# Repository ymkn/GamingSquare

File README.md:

# GamingSquare

A customizable left-hand mechanical keyboard for gaming.

## LICENSE

This project is licensed under the MIT License, see the [LICENSE file](LICENSE) for details.

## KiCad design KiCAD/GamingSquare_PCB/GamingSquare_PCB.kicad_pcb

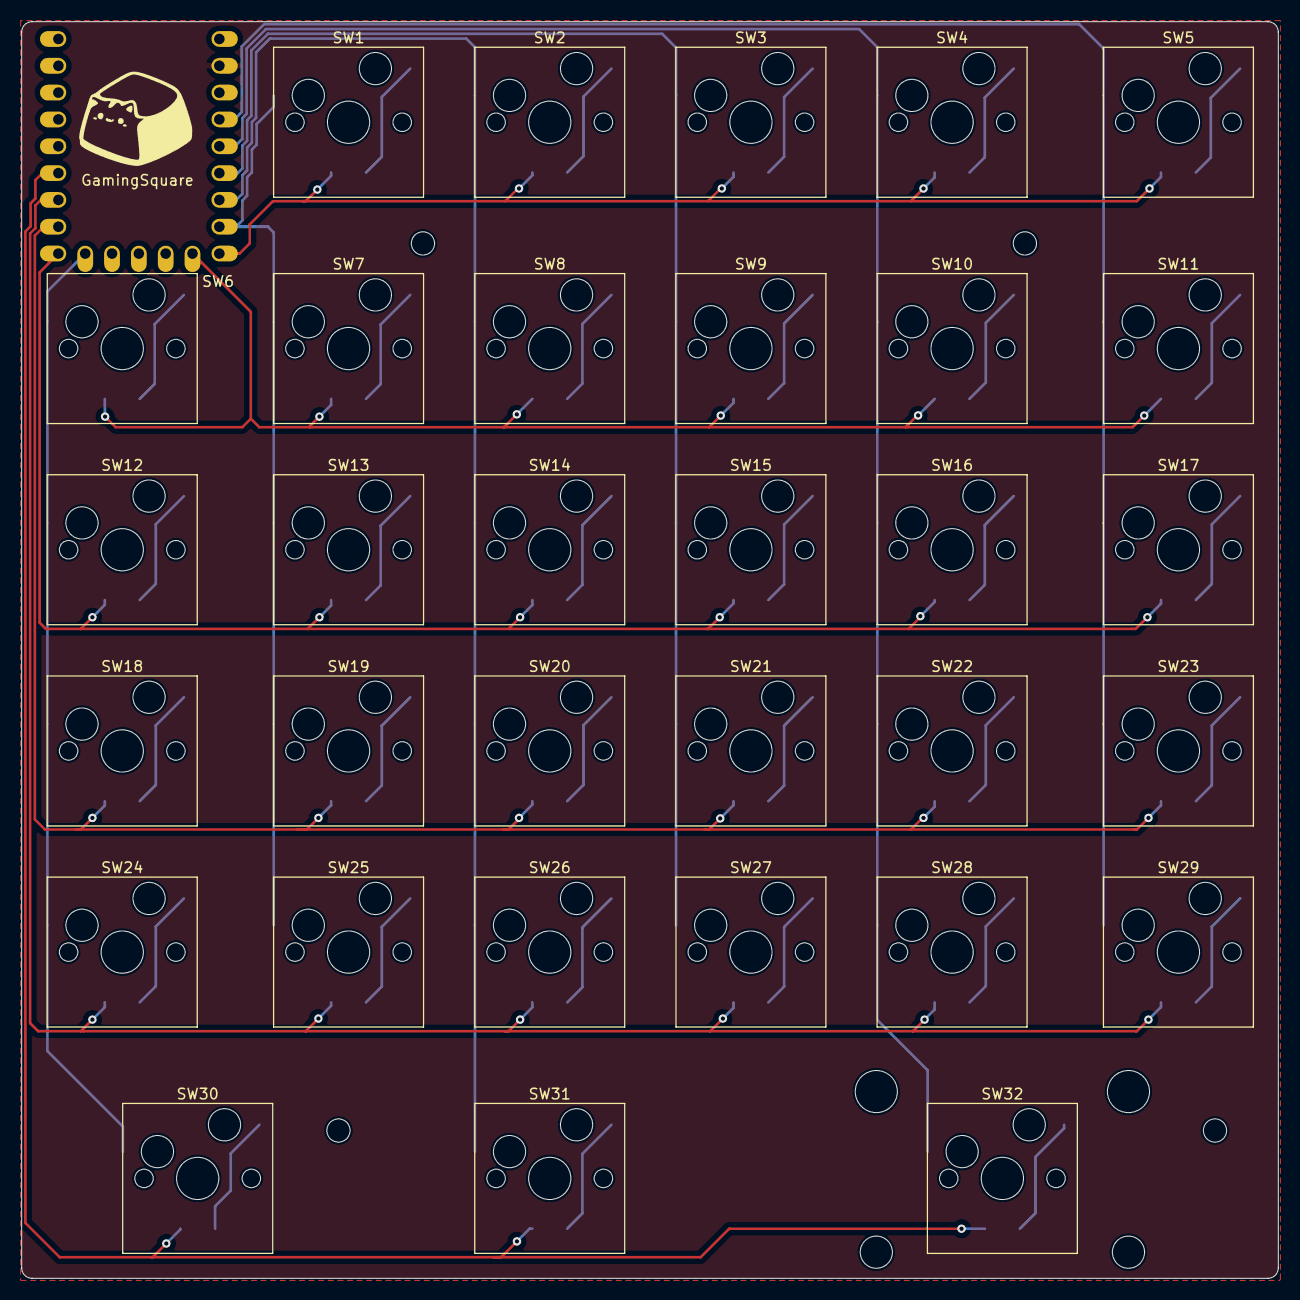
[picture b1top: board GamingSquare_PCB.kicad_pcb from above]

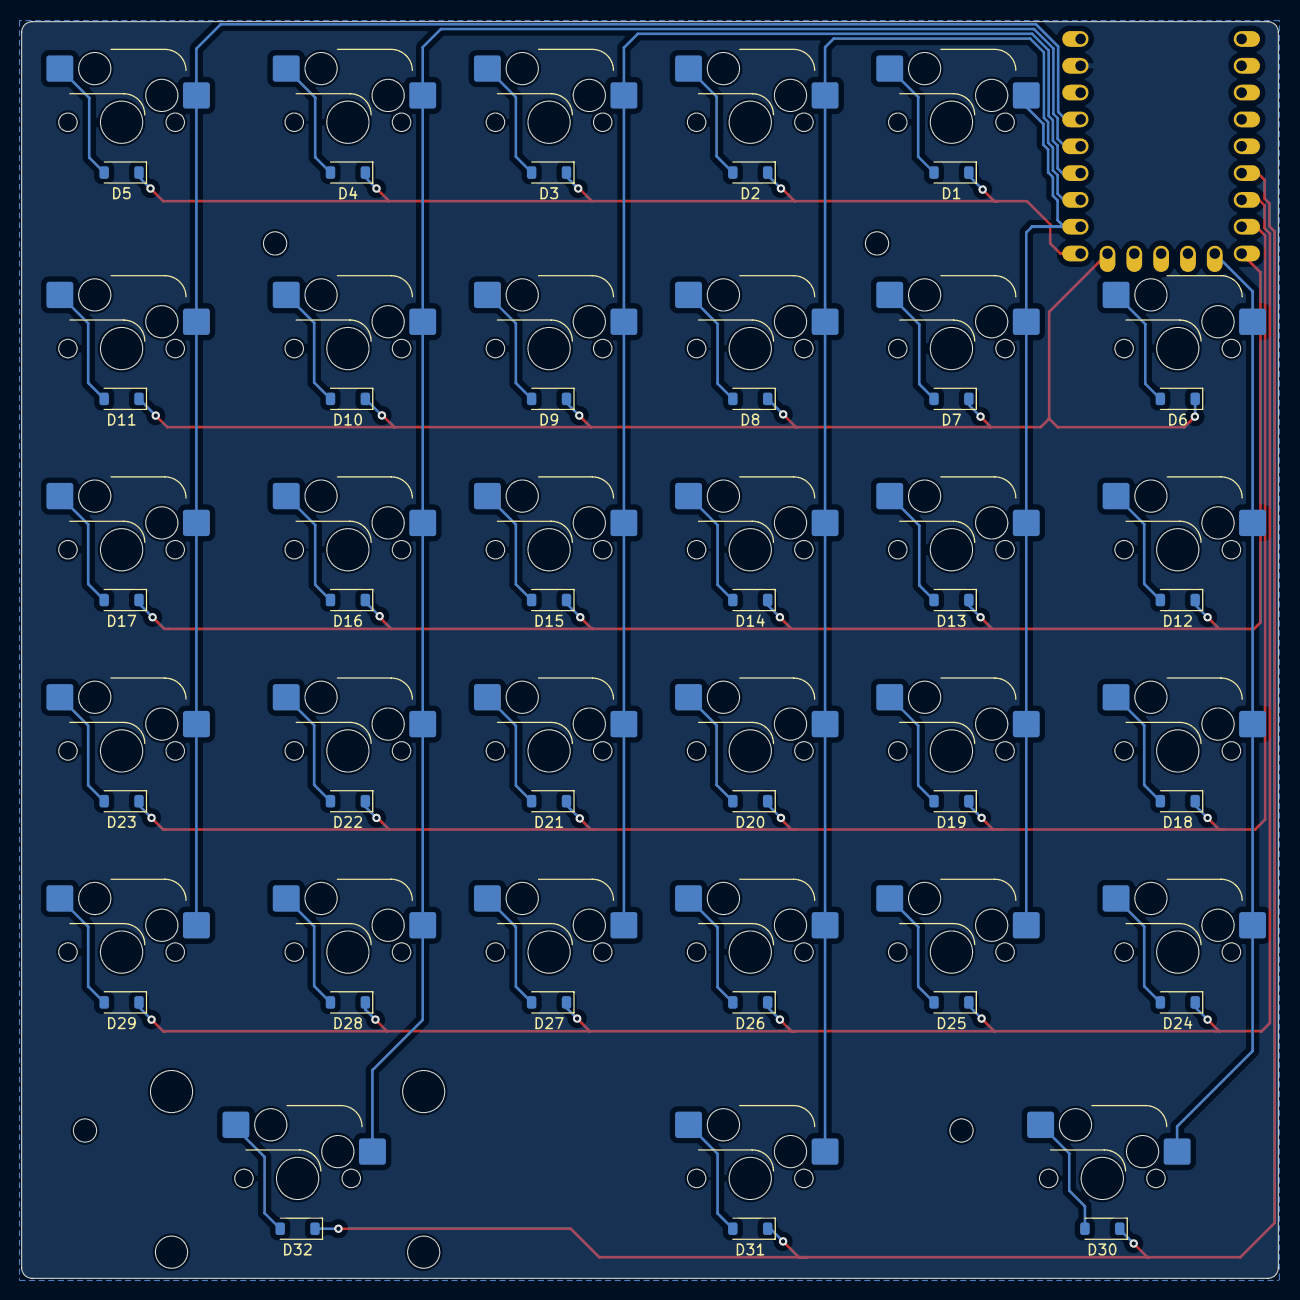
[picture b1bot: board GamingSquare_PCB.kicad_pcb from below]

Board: 2 copper layers, 119.0 x 119.0 mm, 65 parts (33 on the bottom side), 44 nets.

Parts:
D1, D2, D3, D4, D5, D6, D7, D8, D9, D10, D11, D12, D13, D14, D15, D16, D17, D18, D19, D20, D21, D22, D23, D24, D25, D26, D27, D28, D29, D30, D31, D32: 1N4148W; D_SOD-123
SW1, SW2, SW3, SW4, SW5, SW6, SW7, SW8, SW9, SW10, SW11, SW12, SW13, SW14, SW15, SW16, SW17, SW18, SW19, SW20, SW21, SW22, SW23, SW24, SW25, SW26, SW27, SW28, SW29, SW31: SW_Push; SW_Hotswap_Kailh_MX_1.00u
SW30: SW_Push; SW_Hotswap_Kailh_MX_1.75u
SW32: SW_Push; SW_Hotswap_Kailh_MX_2.75u
U1: rp2040-zero; rp2040-zero-tht

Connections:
COL0: SW6.1, SW12.1, SW18.1, SW24.1, SW30.1, U1.10 (9)
COL1: SW1.1, SW7.1, SW13.1, SW19.1, SW25.1, U1.16 (15)
COL2: SW2.1, SW8.1, SW14.1, SW20.1, SW26.1, SW31.1, U1.17 (26)
COL3: SW3.1, SW9.1, SW15.1, SW21.1, SW27.1, U1.18 (27)
COL4: SW4.1, SW10.1, SW16.1, SW22.1, SW28.1, SW32.1, U1.19 (28)
COL5: SW5.1, SW11.1, SW17.1, SW23.1, SW29.1, U1.20 (29)
unnamed: D1.2 (A), SW1.2
unnamed: D2.2 (A), SW2.2
unnamed: D3.2 (A), SW3.2
unnamed: D4.2 (A), SW4.2
unnamed: D5.2 (A), SW5.2
unnamed: D6.2 (A), SW6.2
unnamed: D7.2 (A), SW7.2
unnamed: D8.2 (A), SW8.2
unnamed: D9.2 (A), SW9.2
unnamed: D10.2 (A), SW10.2
unnamed: D11.2 (A), SW11.2
unnamed: D12.2 (A), SW12.2
unnamed: D13.2 (A), SW13.2
unnamed: D14.2 (A), SW14.2
unnamed: D15.2 (A), SW15.2
unnamed: D16.2 (A), SW16.2
unnamed: D17.2 (A), SW17.2
unnamed: D18.2 (A), SW18.2
unnamed: D19.2 (A), SW19.2
unnamed: D20.2 (A), SW20.2
unnamed: D21.2 (A), SW21.2
unnamed: D22.2 (A), SW22.2
unnamed: D23.2 (A), SW23.2
unnamed: D24.2 (A), SW24.2
unnamed: D25.2 (A), SW25.2
unnamed: D26.2 (A), SW26.2
unnamed: D27.2 (A), SW27.2
unnamed: D28.2 (A), SW28.2
unnamed: D29.2 (A), SW29.2
unnamed: D30.2 (A), SW30.2
unnamed: D31.2 (A), SW31.2
unnamed: D32.2 (A), SW32.2
ROW0: D1.1 (K), D2.1 (K), D3.1 (K), D4.1 (K), D5.1 (K), U1.15 (14)
ROW1: D6.1 (K), D7.1 (K), D8.1 (K), D9.1 (K), D10.1 (K), D11.1 (K), U1.14 (13)
ROW2: D12.1 (K), D13.1 (K), D14.1 (K), D15.1 (K), D16.1 (K), D17.1 (K), U1.9 (8)
ROW3: D18.1 (K), D19.1 (K), D20.1 (K), D21.1 (K), D22.1 (K), D23.1 (K), U1.8 (7)
ROW4: D24.1 (K), D25.1 (K), D26.1 (K), D27.1 (K), D28.1 (K), D29.1 (K), U1.7 (6)
ROW5: D30.1 (K), D31.1 (K), D32.1 (K), U1.6 (5)

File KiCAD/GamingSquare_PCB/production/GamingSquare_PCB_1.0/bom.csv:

Designator,Footprint,Quantity,Value,LCSC Part #
"D1, D10, D11, D12, D13, D14, D15, D16, D17, D18, D19, D2, D20, D21, D22, D23, D24, D25, D26, D27, D28, D29, D3, D30, D31, D32, D4, D5, D6, D7, D8, D9",D_SOD-123,32,1N4148W,
"SW1, SW10, SW11, SW12, SW13, SW14, SW15, SW16, SW17, SW18, SW19, SW2, SW20, SW21, SW22, SW23, SW24, SW25, SW26, SW27, SW28, SW29, SW3, SW31, SW4, SW5, SW6, SW7, SW8, SW9",SW_Hotswap_Kailh_MX_1.00u,30,SW_Push,
SW30,SW_Hotswap_Kailh_MX_1.75u,1,SW_Push,
SW32,SW_Hotswap_Kailh_MX_2.75u,1,SW_Push,
U1,rp2040-zero-tht,1,rp2040-zero,

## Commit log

2023-12-04 PRK Firmware追加
2023-12-06 ライセンスファイルの追加
2023-12-10 QMK Firmwareの追加
2024-05-02 ビルドガイドの追加
2024-05-02 ケースデータの表記修正
